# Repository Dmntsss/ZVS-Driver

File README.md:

# ZVS-Driver
This is the attempt of the team ZVS Walkers to create a working ZVS Driver as part of the IEEE Upatras ZVS driver project

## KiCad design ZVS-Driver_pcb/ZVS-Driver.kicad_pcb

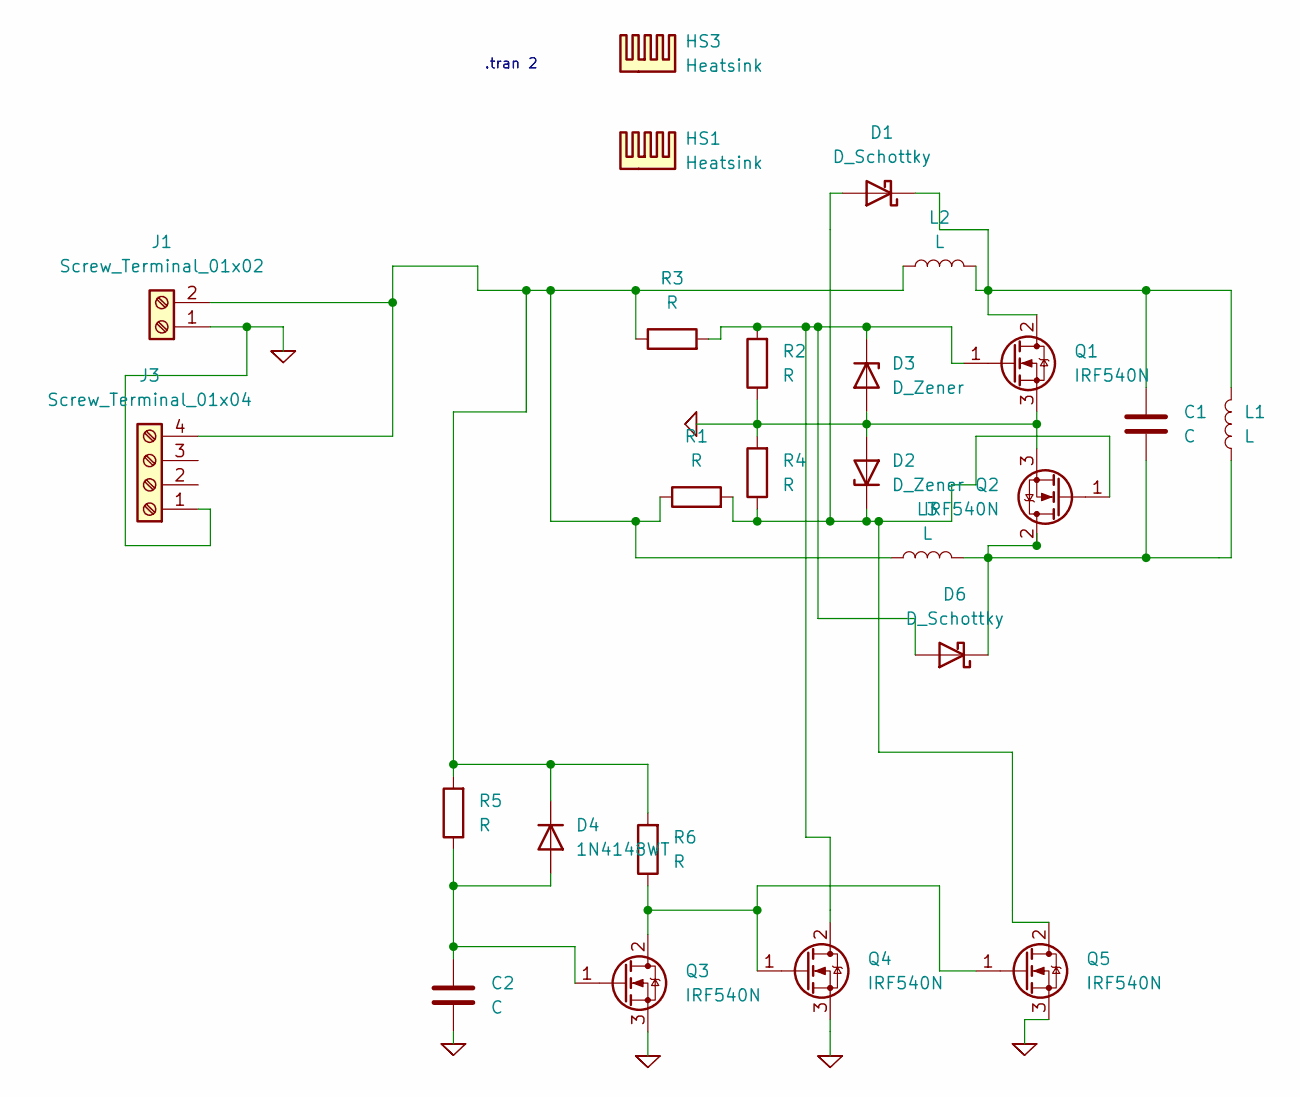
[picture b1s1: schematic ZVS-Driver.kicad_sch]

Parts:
C1: C; C_Rect_L7.2mm_W11.0mm_P5.00mm_FKS2_FKP2_MKS2_MKP2
C2: C; C_Radial_D10.0mm_H20.0mm_P4.5mm,customia
D1, D6: D_Schottky; D_DO-41_SOD81_P12.70mm_Horizontal
D2, D3: D_Zener; D_DO-41_SOD81_P12.70mm_Horizontal
D4: 1N4148WT; D_DO-41_SOD81_P12.70mm_Horizontal
HS1, HS3: Heatsink; Heatsink_Fischer_FK224xx2201_25x8.3mm
J1: Screw_Terminal_01x02; TerminalBlock_Phoenix_MKDS-1,5-2-5.08_1x02_P5.08mm_Horizont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
J3: Screw_Terminal_01x04; usb_c_customia
L1: L; C_Rect_L7.2mm_W11.0mm_P5.00mm_FKS2_FKP2_MKS2_MKP2
L2, L3: L; L_Radial_D10.0mm_P5.00mm_Fastron_07M
Q1, Q2, Q3, Q4, Q5: IRF540N; TO-220-3_Vertical
R1, R2, R3, R4, R5, R6: R; R_Axial_DIN0207_L6.3mm_D2.5mm_P7.62mm_Horizontal

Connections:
0: C2.2, D2.2 (A), D3.2 (A), J1.1, J3.1, Q1.3 (S), Q2.3 (S), Q3.3 (S), Q4.3 (S), Q5.3 (S), R2.1, R4.2
unnamed: D1.2 (A), D2.1 (K), Q2.1 (G), Q5.2 (D), R1.2, R4.1
unnamed: C1.1, D1.1 (K), L1.2, L2.2, Q1.2 (D)
unnamed: D3.1 (K), D6.2 (A), Q1.1 (G), Q4.2 (D), R2.2, R3.2
unnamed: C2.1, D4.2 (A), Q3.1 (G), R5.1
unnamed: D4.1 (K), J1.2, J3.4, L2.1, L3.1, R1.1, R3.1, R5.2, R6.2
unnamed: C1.2, D6.1 (K), L1.1, L3.2, Q2.2 (D)
unnamed: Q3.2 (D), Q4.1 (G), Q5.1 (G), R6.1

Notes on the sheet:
.tran 2

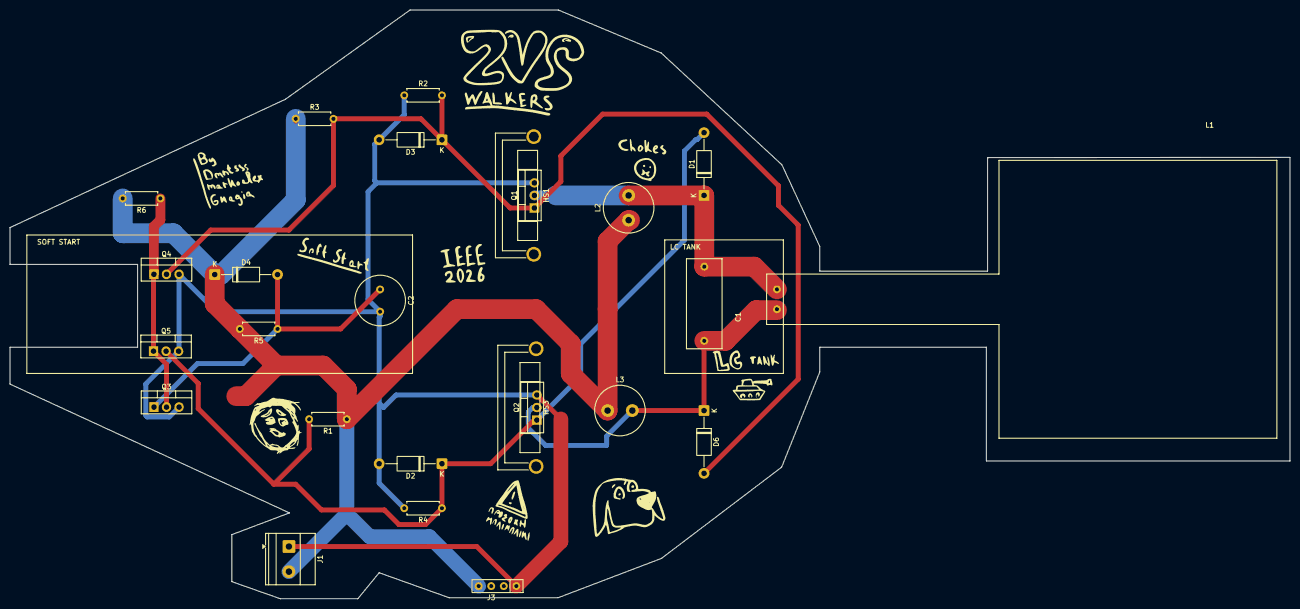
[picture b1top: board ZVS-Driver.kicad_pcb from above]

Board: 2 copper layers, 258.8 x 119.1 mm, 25 parts (0 on the bottom side), 8 nets.

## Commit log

2025-12-06 Add files via upload
    a not finished left part
2025-12-06 Add files via upload
    updated aristera meros (proxeiro)
2025-12-12 Soft start is working
2025-12-18 upload combined
2025-12-20 anapoda oi zeiner
2025-12-20 ebala enan megalo pyknwth gia na meiwsw ta ripples
2025-12-20 neo soft start
2025-12-21 leitourgeiii
2025-12-21 mikroteres zener sta gate
2025-12-21 Add files via upload
    εξεεεεεελ
2025-12-21 Zip for mr tolis
2026-03-01 test
2026-03-01 deleted
2026-03-02 new combined plus pcb design
2026-03-02 delted
2026-03-02 fist pcb design
2026-03-02 idk at this pojnt
2026-03-07 FINAL working asc LTspice model, low voltage for charging
2026-03-07 remove combinedV2.log file
2026-03-11 FINAL FIANL TELIKO FR (xwris regulator kai 5V eisodo)
2026-03-12 Coupled inductors
2026-03-15 updated scematic and footprints assigned
2026-03-15 new after presntation 15/3
2026-03-15 new custom fotprint name
2026-03-16 Allages nikou
2026-03-16 Routing
2026-03-16 updated heatsinks and screw terminal as an input (havnet put the 4 usb c pins)
2026-03-17 xwris to pinio sto kentro
2026-03-19 Pahos apo routes
2026-03-21 usb c eisodos kai routing stis eisodoys
2026-03-21 Spiti alex
2026-03-21 Mosfet fix
2026-03-22 new millennium falcon design and colors for the pcb
2026-03-22 some stuff that need to be added
2026-03-22 Fixes
2026-03-24 Silkscreen
